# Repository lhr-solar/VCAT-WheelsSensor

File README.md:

# VCAT-WheelsSensor
Rev-B branch is Jeslyn's Left Side Wheels Board

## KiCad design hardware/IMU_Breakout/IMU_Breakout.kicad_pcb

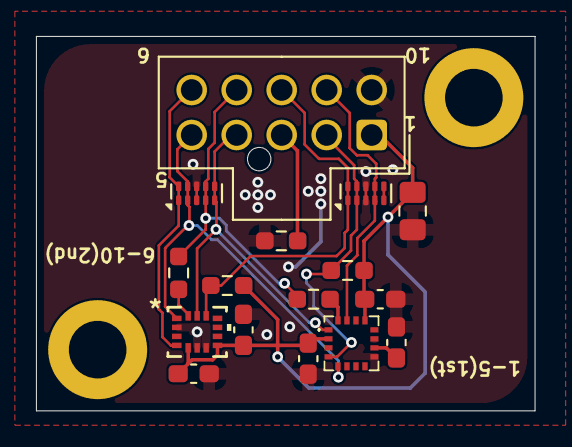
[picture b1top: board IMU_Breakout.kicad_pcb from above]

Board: 2 copper layers, 27.7 x 20.8 mm, 19 parts (1 on the bottom side), 13 nets.

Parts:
C1, C3, C5: 100n; C_0603_1608Metric_Pad1.08x0.95mm_HandSolder
C2: 10u; C_0805_2012Metric_Pad1.18x1.45mm_HandSolder
C4: 10u; C_0603_1608Metric_Pad1.08x0.95mm_HandSolder
C6: 1u; C_0603_1608Metric_Pad1.08x0.95mm_HandSolder
G: LOGO
H1, H3: MountingHole; MountingHole_3.2mm_M3_ISO14580_Pad
IC1: MMC5983MA
IMU_CON: IMU_CON; Molex_Nano-Fit_105310-xx10_2x05_P2.50mm_Vertical
R1, R2: 10k; R_0603_1608Metric_Pad0.98x0.95mm_HandSolder
R3: 0; R_0603_1608Metric_Pad0.98x0.95mm_HandSolder
R4, R5: 22; R_0603_1608Metric_Pad0.98x0.95mm_HandSolder
U1: ASM330LHHX; LGA14_ASM330_STM
U2, U3: TPD4E05U06DQA; USON-10_2.5x1.0mm_P0.5mm

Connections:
+3.3V: C1.1, C2.1, C3.1, C5.1, C6.1, IC1.2 (VDD), IC1.13 (VDDIO), IMU_CON.1, R1.2, R2.2, U1.5 (VDDIO), U1.8 (VDD)
/IMU_CS: IMU_CON.8, R1.1, U1.12 (CS), U3.1 (D1+), U3.10 (NC)
/IMU_INT: IMU_CON.6, U1.4 (INT1), U2.1 (D1+), U2.10 (NC)
/IMUs/IMU_MOSI: R5.1, U1.14 (SDA)
/IMUs/MAG_MOSI: IC1.16 (SDA/SPI_SDI), R4.1
/MAG_CS: IC1.4 (SPI_CS), IMU_CON.2, R2.1, U3.2 (D1-), U3.9 (NC)
/MAG_DRDY: IC1.15 (INT), IMU_CON.9, U3.4 (D2+), U3.7 (NC)
/SPI_MISO: IC1.5 (SPI_SDO), IMU_CON.5, U1.1 (SDO/SA0), U2.2 (D1-), U2.9 (NC)
/SPI_MOSI: IMU_CON.7, R4.2, R5.2, U2.4 (D2+), U2.7 (NC)
/SPI_SCK: IC1.1 (SCL/SPI_SCK), IMU_CON.4, U1.13 (SCL), U2.5 (D2-), U2.6 (NC)
GND: C1.2, C2.2, C3.2, C4.2, C5.2, C6.2, IC1.9 (GND_1), IC1.11 (GND_2), IMU_CON.10, R3.1, U1.2 (RES), U1.3 (RES), U1.6 (GND), U1.7 (GND), U2.3 (GND), U2.8 (GND), U3.3 (GND), U3.8 (GND)
unnamed: C4.1, IC1.10 (CAP)
unnamed: IMU_CON.3, R3.2

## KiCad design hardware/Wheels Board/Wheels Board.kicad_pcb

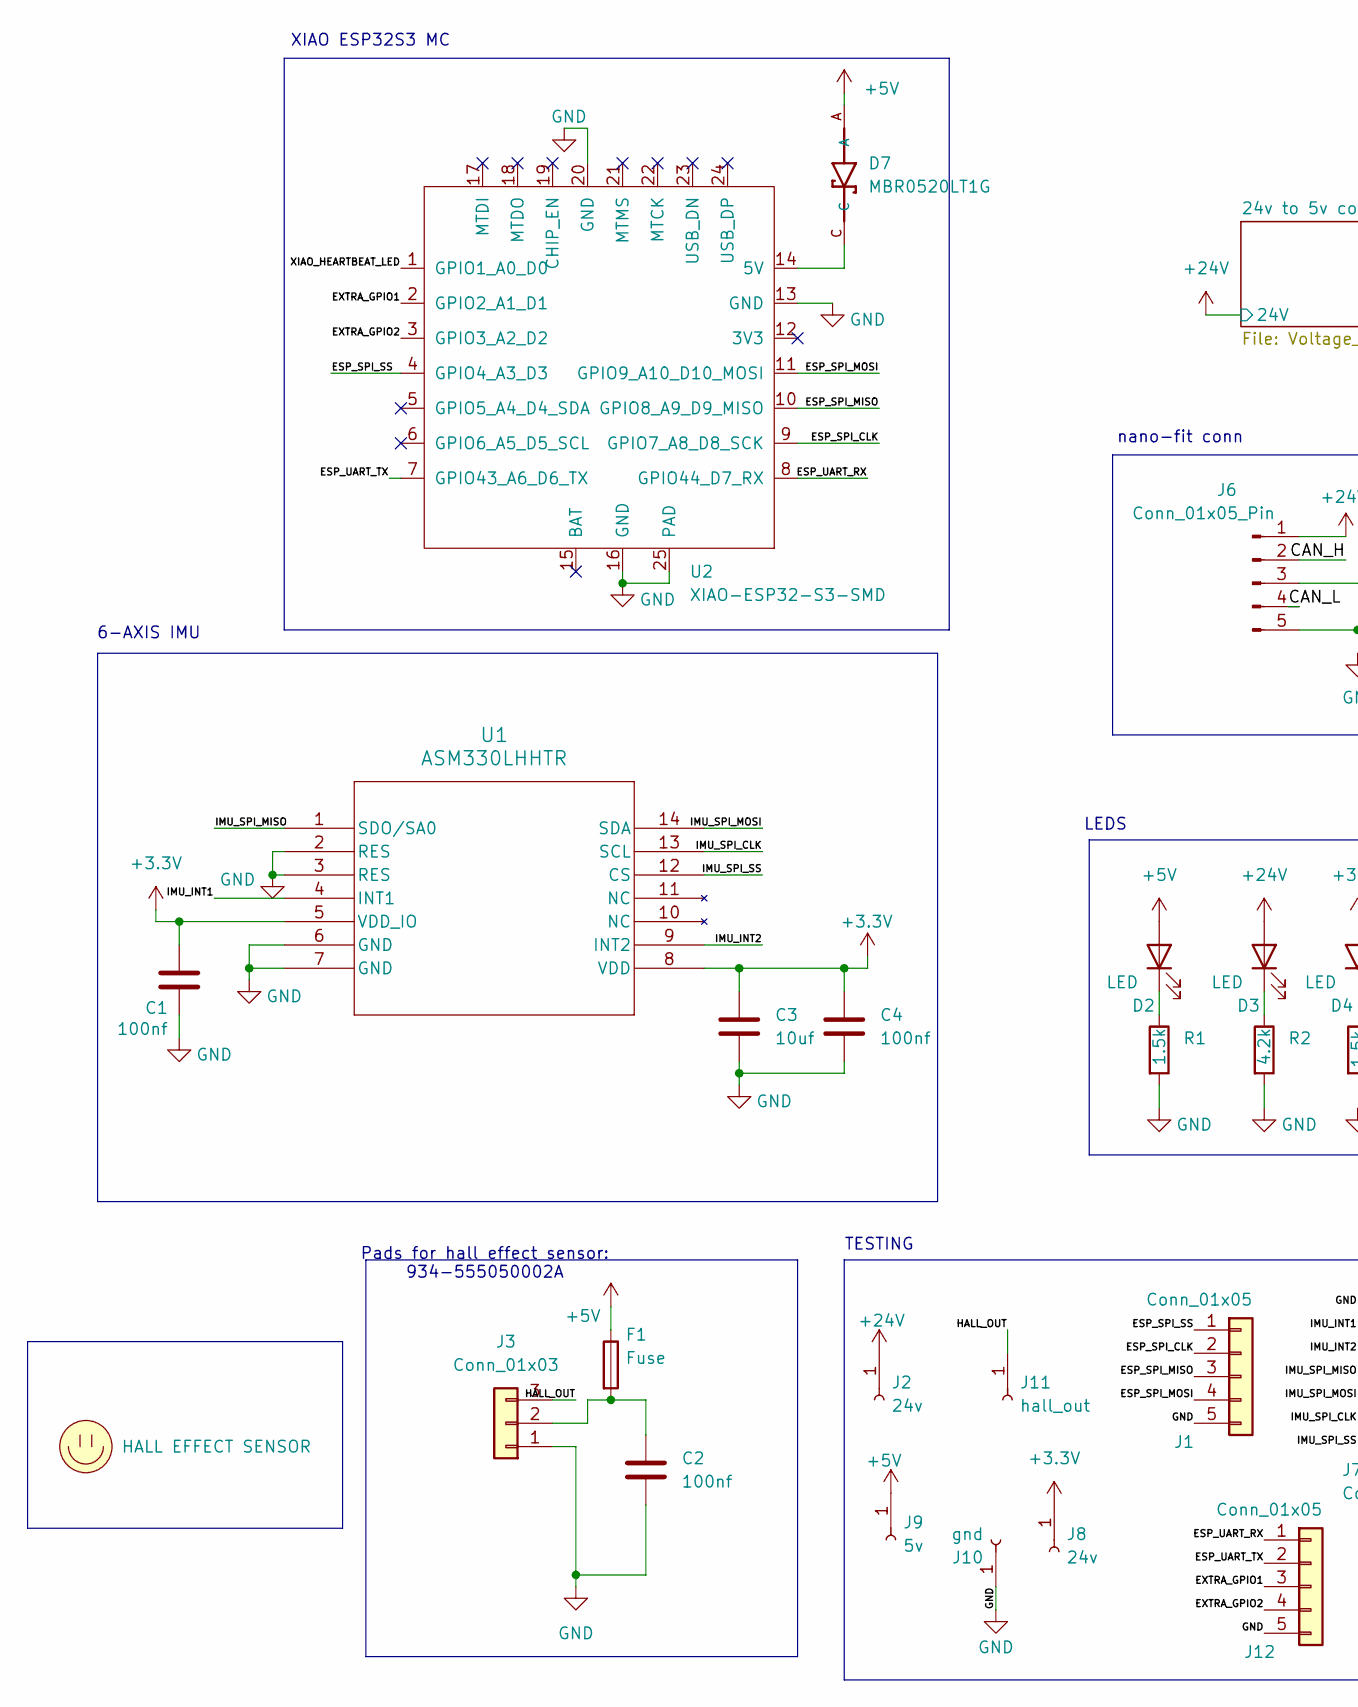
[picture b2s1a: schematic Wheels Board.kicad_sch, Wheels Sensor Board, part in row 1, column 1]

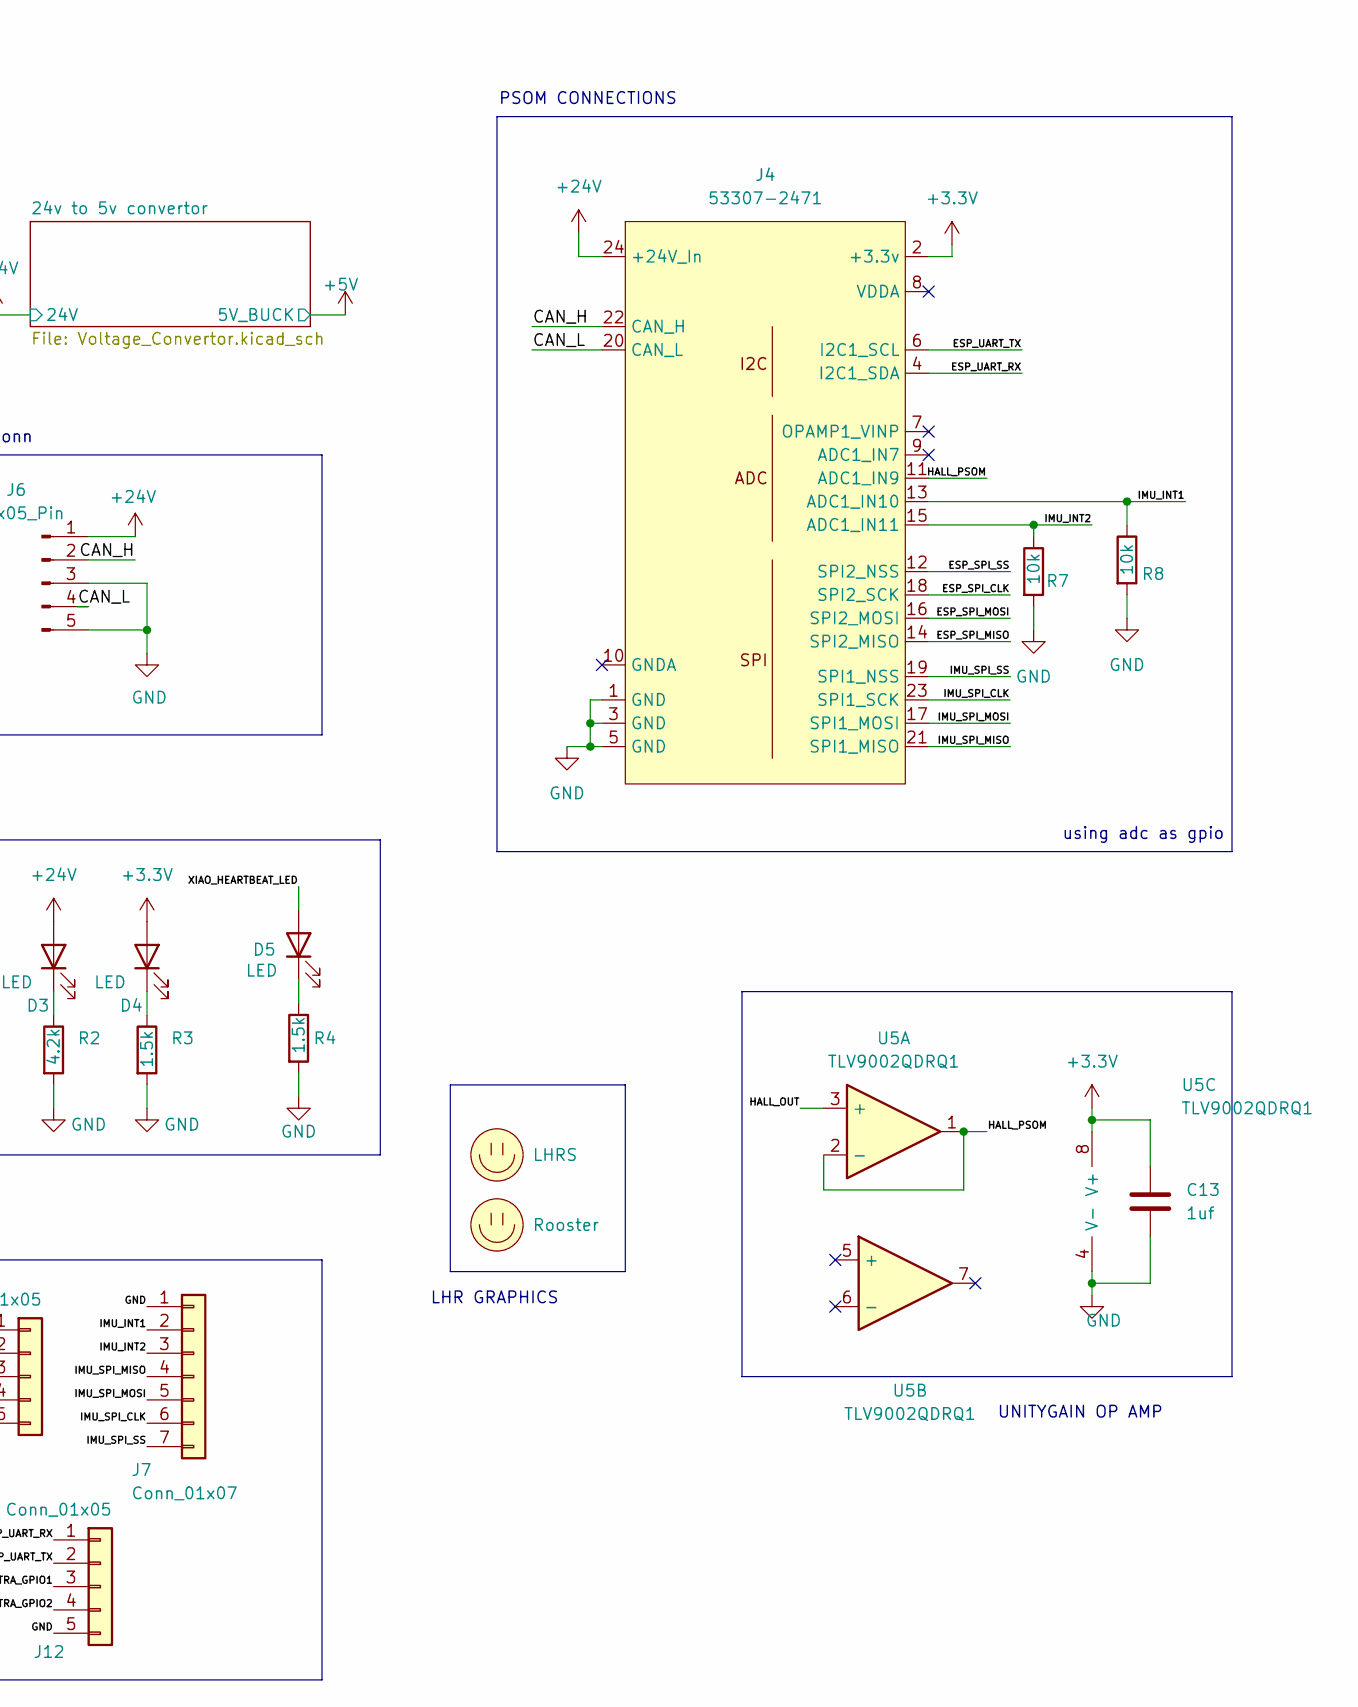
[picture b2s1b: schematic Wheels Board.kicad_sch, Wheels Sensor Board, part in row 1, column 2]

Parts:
C1, C2, C4: 100nf; C_0603_1608Metric_Pad1.08x0.95mm_HandSolder
C3: 10uf; C_0603_1608Metric_Pad1.08x0.95mm_HandSolder
C13: 1uf; C_0603_1608Metric_Pad1.08x0.95mm_HandSolder
D2, D3, D4, D5: LED; LED_0603_1608Metric_Pad1.05x0.95mm_HandSolder
D7: MBR0520LT1G; SOD3716X135N
F1: Fuse; FUSE_3568
J1, J12: Conn_01x05; PinHeader_1x05_P2.54mm_Vertical
J2, J8: 24v; PinHeader_1x01_P2.54mm_Vertical
J3: Conn_01x03; 105313-1103
J4: 53307-2471; PeripheralSOM
J6: Conn_01x05_Pin; Molex_Nano-Fit_105313-xx04_1x04_P2.50mm_Horizontal
J7: Conn_01x07; PinHeader_1x07_P2.54mm_Vertical
J9: 5v; PinHeader_1x01_P2.54mm_Vertical
J10: gnd; PinHeader_1x01_P2.54mm_Vertical
J11: hall_out; PinHeader_1x01_P2.54mm_Vertical
LOGO1: LHRS; LHRs_LOGO
LOGO2: Rooster; roosters
LOGO3: HALL EFFECT SENSOR
R1, R3, R4: 1.5k; R_0603_1608Metric_Pad0.98x0.95mm_HandSolder
R2: 4.2k; R_0603_1608Metric_Pad0.98x0.95mm_HandSolder
R7, R8: 10k; R_0603_1608Metric_Pad0.98x0.95mm_HandSolder
U1: ASM330LHHTR; LGA-14L_2P5X3X0P83_STM
U2: XIAO-ESP32-S3-SMD; XIAO-ESP32S3-DIP
U5: TLV9002QDRQ1; SOIC-8_3.9x4.9mm_P1.27mm; Mouser P/N 595-TLV9002QDRQ1

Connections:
+3.3V: C1.1, C3.1, C4.1, C13.1, D4.2 (A), J4.2 (+3.3v), J8.1, U1.5 (VDD_IO), U1.8 (VDD), U5.8 (V+)
+5V: D2.2 (A), D7.A, F1.1, J9.1; also elsewhere on the board
+24V: D3.2 (A), J2.1, J4.24 (+24V_In), J6.1; also elsewhere on the board
/CAN_H: J4.22 (CAN_H), J6.2
/CAN_L: J4.20 (CAN_L), J6.4
/ESP_SPI_CLK: J1.2, J4.18 (SPI2_SCK), U2.9 (GPIO7_A8_D8_SCK)
/ESP_SPI_MISO: J1.3, J4.14 (SPI2_MISO), U2.10 (GPIO8_A9_D9_MISO)
/ESP_SPI_MOSI: J1.4, J4.16 (SPI2_MOSI), U2.11 (GPIO9_A10_D10_MOSI)
/ESP_SPI_SS: J1.1, J4.12 (SPI2_NSS), U2.4 (GPIO4_A3_D3)
/ESP_UART_RX: J4.4 (I2C1_SDA), J12.1, U2.8 (GPIO44_D7_RX)
/ESP_UART_TX: J4.6 (I2C1_SCL), J12.2, U2.7 (GPIO43_A6_D6_TX)
/EXTRA_GPIO1: J12.3, U2.2 (GPIO2_A1_D1)
/EXTRA_GPIO2: J12.4, U2.3 (GPIO3_A2_D2)
/HALL_OUT: J3.3, J11.1, U5.3 (+)
/HALL_PSOM: J4.11 (ADC1_IN9), U5.1, U5.2 (-)
/IMU_INT1: J4.13 (ADC1_IN10), J7.2, R8.1, U1.4 (INT1)
/IMU_INT2: J4.15 (ADC1_IN11), J7.3, R7.1, U1.9 (INT2)
/IMU_SPI_CLK: J4.23 (SPI1_SCK), J7.6, U1.13 (SCL)
/IMU_SPI_MISO: J4.21 (SPI1_MISO), J7.4, U1.1 (SDO/SA0)
/IMU_SPI_MOSI: J4.17 (SPI1_MOSI), J7.5, U1.14 (SDA)
/IMU_SPI_SS: J4.19 (SPI1_NSS), J7.7, U1.12 (CS)
/XIAO_HEARTBEAT_LED: D5.2 (A), U2.1 (GPIO1_A0_D0)
GND: C1.2, C2.2, C3.2, C4.2, C13.2, J1.5, J3.1, J4.1 (GND), J4.3 (GND), J4.5 (GND), J6.3, J6.5, J7.1, J10.1, J12.5, R1.2, R2.2, R3.2, R4.2, R7.2, R8.2, U1.2 (RES), U1.3 (RES), U1.6 (GND), U1.7 (GND), U2.13 (GND), U2.16 (GND), U2.20 (GND), U2.25 (PAD), U5.4 (V-); also elsewhere on the board
unnamed: D2.1 (K), R1.1
unnamed: D3.1 (K), R2.1
unnamed: D4.1 (K), R3.1
unnamed: D5.1 (K), R4.1
unnamed: C2.1, F1.2, J3.2
unnamed: D7.C, U2.14 (5V)

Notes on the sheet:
LEDS
UNITYGAIN OP AMP
nano-fit conn
Pads for hall effect sensor: 934-555050002A
LHR GRAPHICS
XIAO ESP32S3 MC
PSOM CONNECTIONS
6-AXIS IMU
TESTING
using adc as gpio

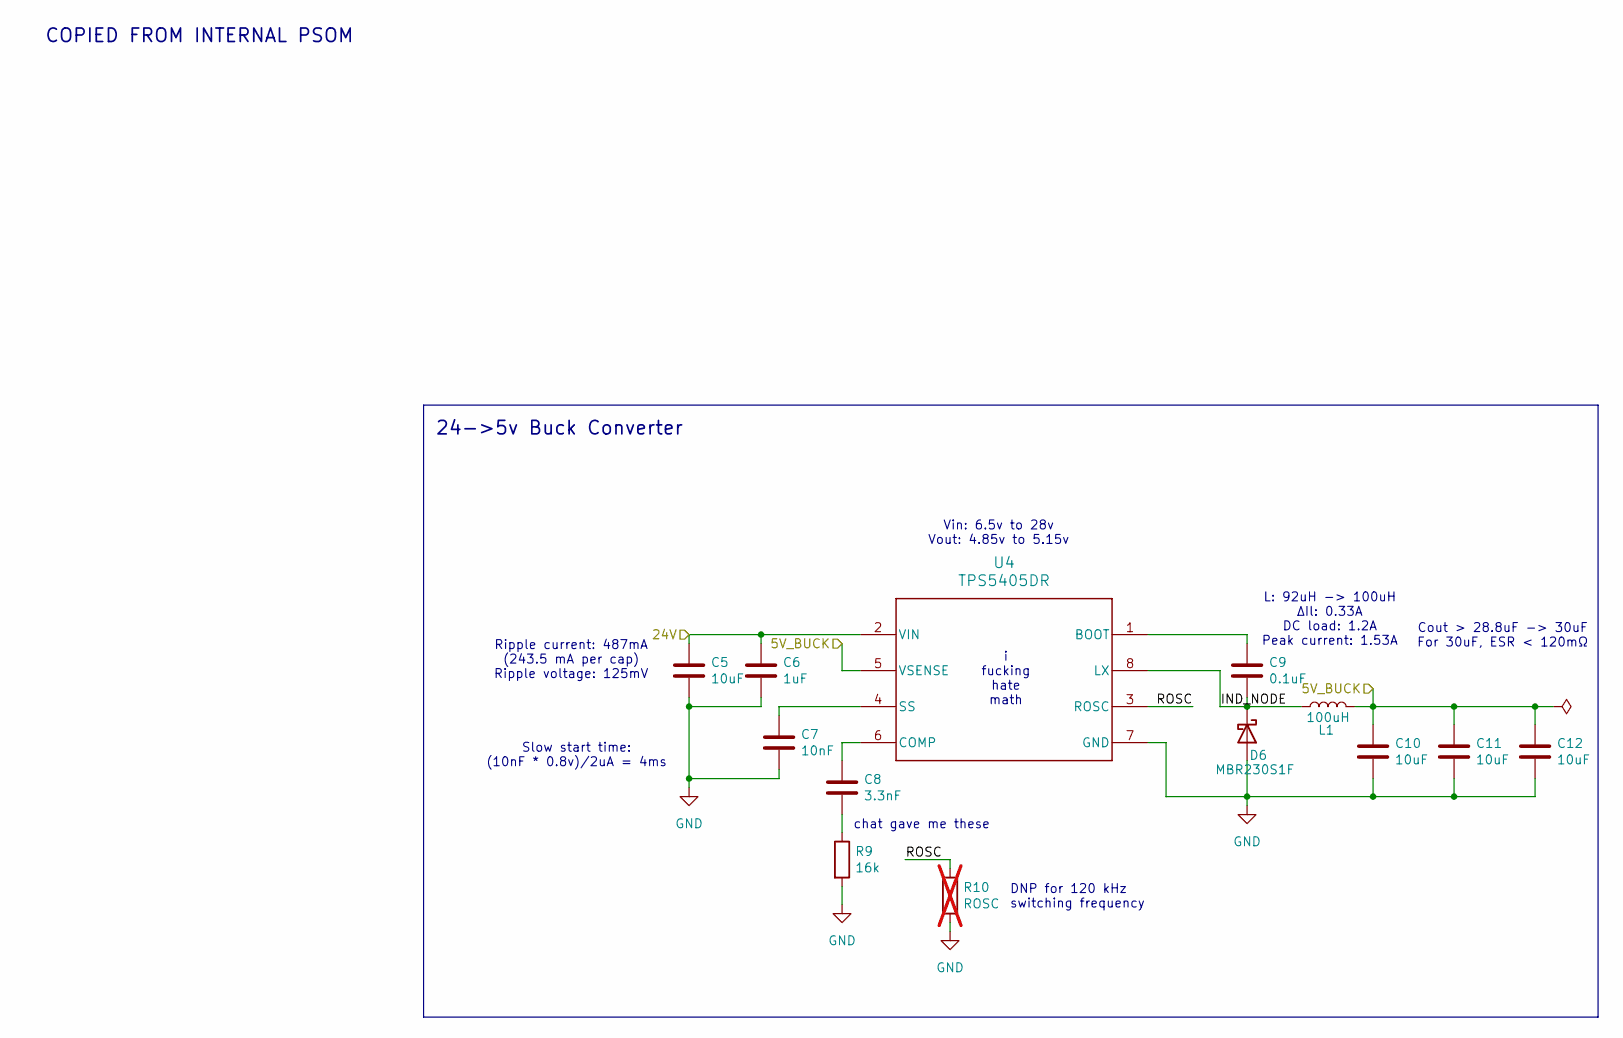
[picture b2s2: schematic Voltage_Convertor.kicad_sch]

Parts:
C5, C10, C11, C12: 10uF; C_0603_1608Metric_Pad1.08x0.95mm_HandSolder
C6: 1uF; C_0603_1608Metric_Pad1.08x0.95mm_HandSolder
C7: 10nF; C_0603_1608Metric_Pad1.08x0.95mm_HandSolder
C8: 3.3nF; C_0603_1608Metric_Pad1.08x0.95mm_HandSolder
C9: 0.1uF; C_0603_1608Metric_Pad1.08x0.95mm_HandSolder
D6: MBR230S1F; D_SOD-323_HandSoldering
L1: 100uH; L_Coilcraft_MSS1246-XXX
R9: 16k; R_0603_1608Metric_Pad0.98x0.95mm_HandSolder
R10: ROSC; R_0603_1608Metric_Pad0.98x0.95mm_HandSolder; not fitted
U4: TPS5405DR

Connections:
+5V: C10.1, C11.1, C12.1, L1.2, U4.5 (VSENSE); also elsewhere on the board
+24V: C5.1, C6.1, U4.2 (VIN); also elsewhere on the board
/24v to 5v convertor/IND_NODE: C9.2, D6.1 (K), L1.1, U4.8 (LX)
/24v to 5v convertor/ROSC: R10.1, U4.3 (ROSC)
GND: C5.2, C6.2, C7.2, C10.2, C11.2, C12.2, D6.2 (A), R9.2, R10.2, U4.7 (GND); also elsewhere on the board
unnamed: C8.2, R9.1
unnamed: C9.1, U4.1 (BOOT)
unnamed: C8.1, U4.6 (COMP)
unnamed: C7.1, U4.4 (SS)

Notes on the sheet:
i fucking hate math
chat gave me these
Vin: 6.5v to 28v Vout: 4.85v to 5.15v
Slow start time: (10nF * 0.8v)/2uA = 4ms
DNP for 120 kHz switching frequency
Cout > 28.8uF -> 30uF For 30uF, ESR < 120mΩ
L: 92uH -> 100uH ΔIl: 0.33A DC load: 1.2A Peak current: 1.53A
COPIED FROM INTERNAL PSOM
24->5v Buck Converter
Ripple current: 487mA (243.5 mA per cap) Ripple voltage: 125mV

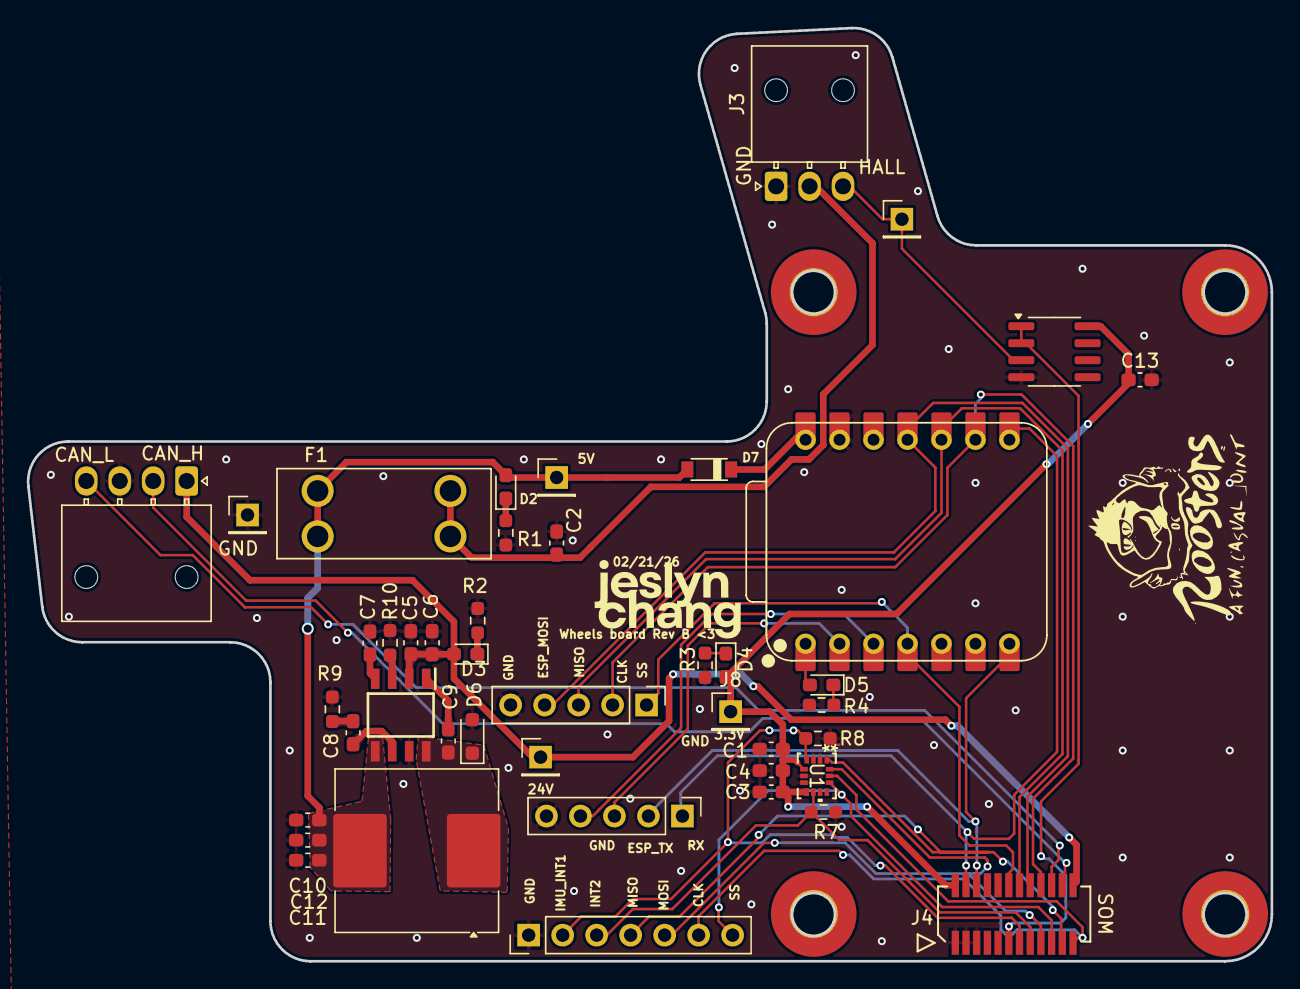
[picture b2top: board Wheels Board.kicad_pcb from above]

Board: 2 copper layers, 92.9 x 69.7 mm, 45 parts (0 on the bottom side), 35 nets.

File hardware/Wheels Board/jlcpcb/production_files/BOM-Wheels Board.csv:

Comment,Designator,Footprint,LCSC,Quantity
0.1uF,C9,C_0603_1608Metric_Pad1.08x0.95mm_HandSolder,C14663,1
1.5k,"R1,R4",R_0603_1608Metric_Pad0.98x0.95mm_HandSolder,C22843,2
1.5k,R3,R_0603_1608Metric_Pad0.98x0.95mm_HandSolder,C96693,1
100nf,"C1,C2,C4",C_0603_1608Metric_Pad1.08x0.95mm_HandSolder,C14663,3
10k,"R7,R8",R_0603_1608Metric_Pad0.98x0.95mm_HandSolder,C25804,2
10nF,C7,C_0603_1608Metric_Pad1.08x0.95mm_HandSolder,C57112,1
10uF,"C10,C11,C12,C5",C_0603_1608Metric_Pad1.08x0.95mm_HandSolder,C440198,4
10uf,C3,C_0603_1608Metric_Pad1.08x0.95mm_HandSolder,C440198,1
16k,R9,R_0603_1608Metric_Pad0.98x0.95mm_HandSolder,C137788,1
1uF,C6,C_0603_1608Metric_Pad1.08x0.95mm_HandSolder,C15849,1
1uf,C13,C_0603_1608Metric_Pad1.08x0.95mm_HandSolder,C15849,1
3.3nF,C8,C_0603_1608Metric_Pad1.08x0.95mm_HandSolder,C107088,1
4.2k,R2,R_0603_1608Metric_Pad0.98x0.95mm_HandSolder,C2907165,1
ASM330LHHTR,U1,LGA-14L_2P5X3X0P83_STM,C459826,1
Fuse,F1,FUSE_3568,C5249699,1
LED,"D2,D3,D4,D5",LED_0603_1608Metric_Pad1.05x0.95mm_HandSolder,C84263,4
MBR0520LT1G,D7,SOD3716X135N,C23848,1
MBR230S1F,D6,D_SOD-323_HandSoldering,C111630,1
TLV9002QDRQ1,U5,SOIC-8_3.9x4.9mm_P1.27mm,C2860922,1
TPS5405DR,U4,TPS5405DR,C488409,1
XIAO-ESP32-S3-SMD,U2,XIAO-ESP32S3-DIP,C9900124959,1
hall_out,J11,PinHeader_1x01_P2.54mm_Vertical,,1
Conn_01x07,J7,PinHeader_1x07_P2.54mm_Vertical,,1
Conn_01x05_Pin,J6,Molex_Nano-Fit_105313-xx04_1x04_P2.50mm_Horizontal,,1
Rooster,LOGO2,roosters,,1
24v,J2,PinHeader_1x01_P2.54mm_Vertical,,1
Conn_01x05,J12,PinHeader_1x05_P2.54mm_Vertical,,1
5v,J9,PinHeader_1x01_P2.54mm_Vertical,,1
gnd,J10,PinHeader_1x01_P2.54mm_Vertical,,1
53307-2471,J4,PeripheralSOM,,1
Conn_01x03,J3,105313-1103,,1
24v,J8,PinHeader_1x01_P2.54mm_Vertical,,1
Conn_01x05,J1,PinHeader_1x05_P2.54mm_Vertical,,1
100uH,L1,L_Coilcraft_MSS1246-XXX,,1

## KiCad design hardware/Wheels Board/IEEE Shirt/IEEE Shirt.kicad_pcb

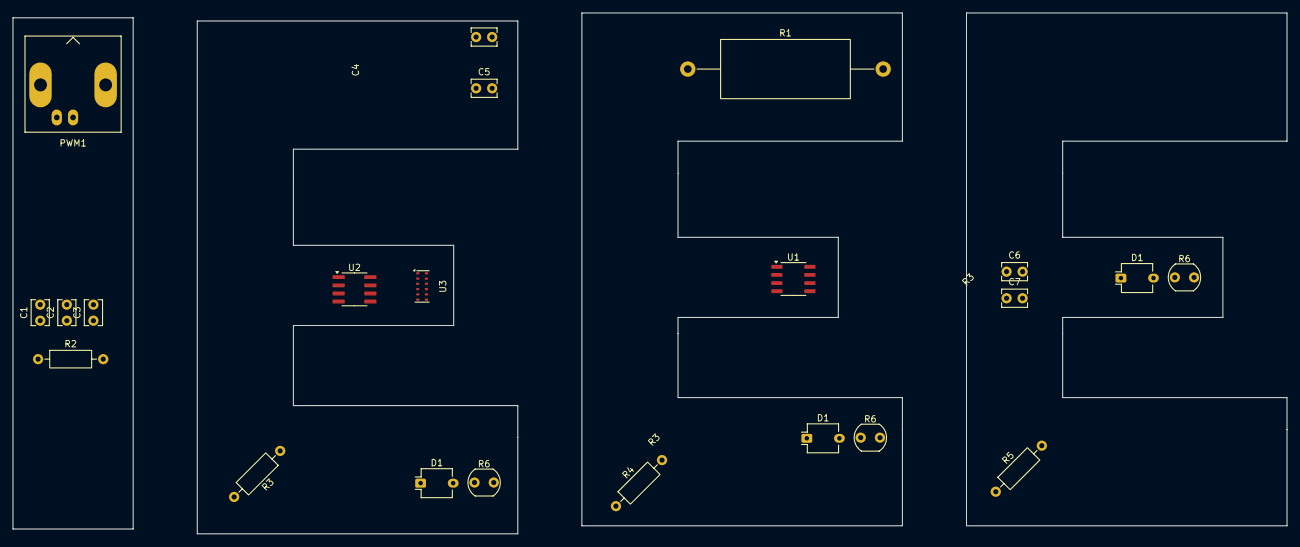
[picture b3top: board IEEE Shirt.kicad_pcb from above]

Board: 2 copper layers, 198.8 x 81.2 mm, 22 parts (0 on the bottom side), 10 nets, no tracks yet.

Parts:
C1, C2, C3: 10u; C_Disc_D3.8mm_W2.6mm_P2.50mm
C4, C5, C6, C7: 1u; C_Disc_D3.8mm_W2.6mm_P2.50mm
D1, D1#2, D1#3: BPW34; Osram_DIL2_4.3x4.65mm_P5.08mm
PWM1: Conn_Coaxial; BNC_Amphenol_B6252HB-NPP3G-50_Horizontal
R1: 0.5; R_Axial_DIN0922_L20.0mm_D9.0mm_P30.48mm_Horizontal
R2: 5k; R_Axial_DIN0207_L6.3mm_D2.5mm_P10.16mm_Horizontal
R3: 20k; R_Axial_DIN0207_L6.3mm_D2.5mm_P10.16mm_Horizontal
R4, R5: 100; R_Axial_DIN0207_L6.3mm_D2.5mm_P10.16mm_Horizontal
R6, R6#2, R6#3: A9013; R_LDR_5.0x4.1mm_P3mm_Vertical
U1: TLV2372; SO-8_3.9x4.9mm_P1.27mm
U2: ACS715xLCTR-20A; SOIC-8_3.9x4.9mm_P1.27mm
U3: TMF8820; AMS_OLGA12

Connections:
10V: C6.2, C7.1, U1.8 (V+)
GND: C1.2, C2.2, C3.2, C6.1, C7.2, PWM1.2 (Ext), R1.1, R2.1, U1.4 (V-)
unnamed: R2.2, R3.1, U1.2 (-)
unnamed: U2.1 (IP+), U2.2 (IP+)
unnamed: U2.3 (IP-), U2.4 (IP-)
unnamed: U3.2 (GND), U3.8 (GND), U3.11 (GND)
unnamed: U3.1 (VDD), U3.7 (VDD), U3.12 (VDD)
OPAMP_OUT: R3.2, U1.1
Vin+: C1.1, C2.1, C3.1
Vout-: C4.2, R1.2, U1.3 (+)

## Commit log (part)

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2025-10-04 added kicad files
2025-10-04 sharepoint
2025-10-10 current rev a
2025-10-16 schematic v1
2025-10-25 Rev a final draft
2025-10-25 footprints
2025-10-25 +op amp, breakout, footprints
2025-10-25 switched to pads for hall sensor wires
2025-10-25 layout planning
2025-10-30 added uart to sch
2025-11-05 concepts of revA layout
2025-11-07 review council changes, layout not finalized
2025-11-08 pre wiring layout
2025-11-08 revised layout again
2025-11-08 revised layout
2025-11-11 new board dimensions
2025-11-13 final revisions!
    i didnt do pn yet
2025-11-13 pre-2.4mm connector experiment
    (will jump back to this if all goes wrong)
2025-11-13 pls pls pls
2025-11-13 final rev a labels added
2025-11-13 silkscreen changes
2025-11-13 Resolved DRC errors
2025-11-15 generated bom
2025-11-15 added hall effect sensor PN
2025-11-15 bom csv
2025-12-19 Wheels Board Rev A (#3)
    * current rev a
    * schematic v1
    * Rev a final draft
    * footprints
    * +op amp, breakout, footprints
    * switched to pads for hall sensor wires
2026-01-31 50% of i2c
2026-01-31 Left rev b layout
2026-01-31 drc changes
2026-02-05 i2c high and low works
2026-02-07 working i2c!!!
2026-02-07 its printing!!!
2026-02-15 ignore invert file for now
2026-02-15 silkscreen final
2026-02-15 silkscreen final2
2026-02-21 conn changes
    rotated can conn, changed hall conn to hor, fixed tp clearance
2026-02-21 remove old prod files
2026-02-21 remove empty file
2026-02-27 added right side
2026-02-27 lcsc
2026-02-28 added bypass cap to hall
2026-02-28 changed hall conn, silkscreen fix
2026-03-01 last changes in bom
2026-03-07 working can!
2026-03-08 transmit and recieve working
2026-04-12 some something it works can tx and rx
